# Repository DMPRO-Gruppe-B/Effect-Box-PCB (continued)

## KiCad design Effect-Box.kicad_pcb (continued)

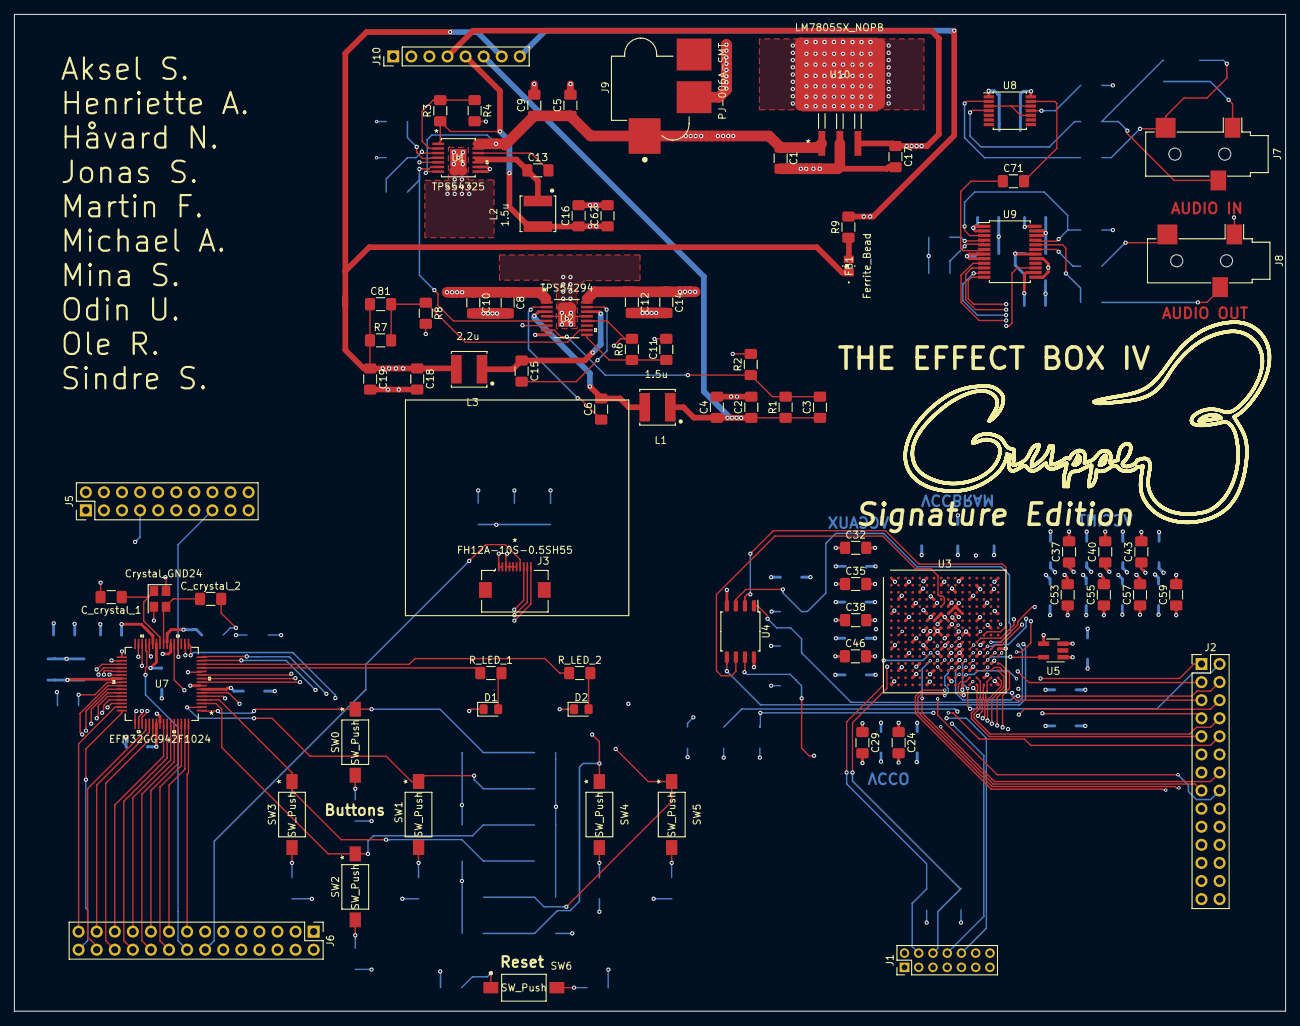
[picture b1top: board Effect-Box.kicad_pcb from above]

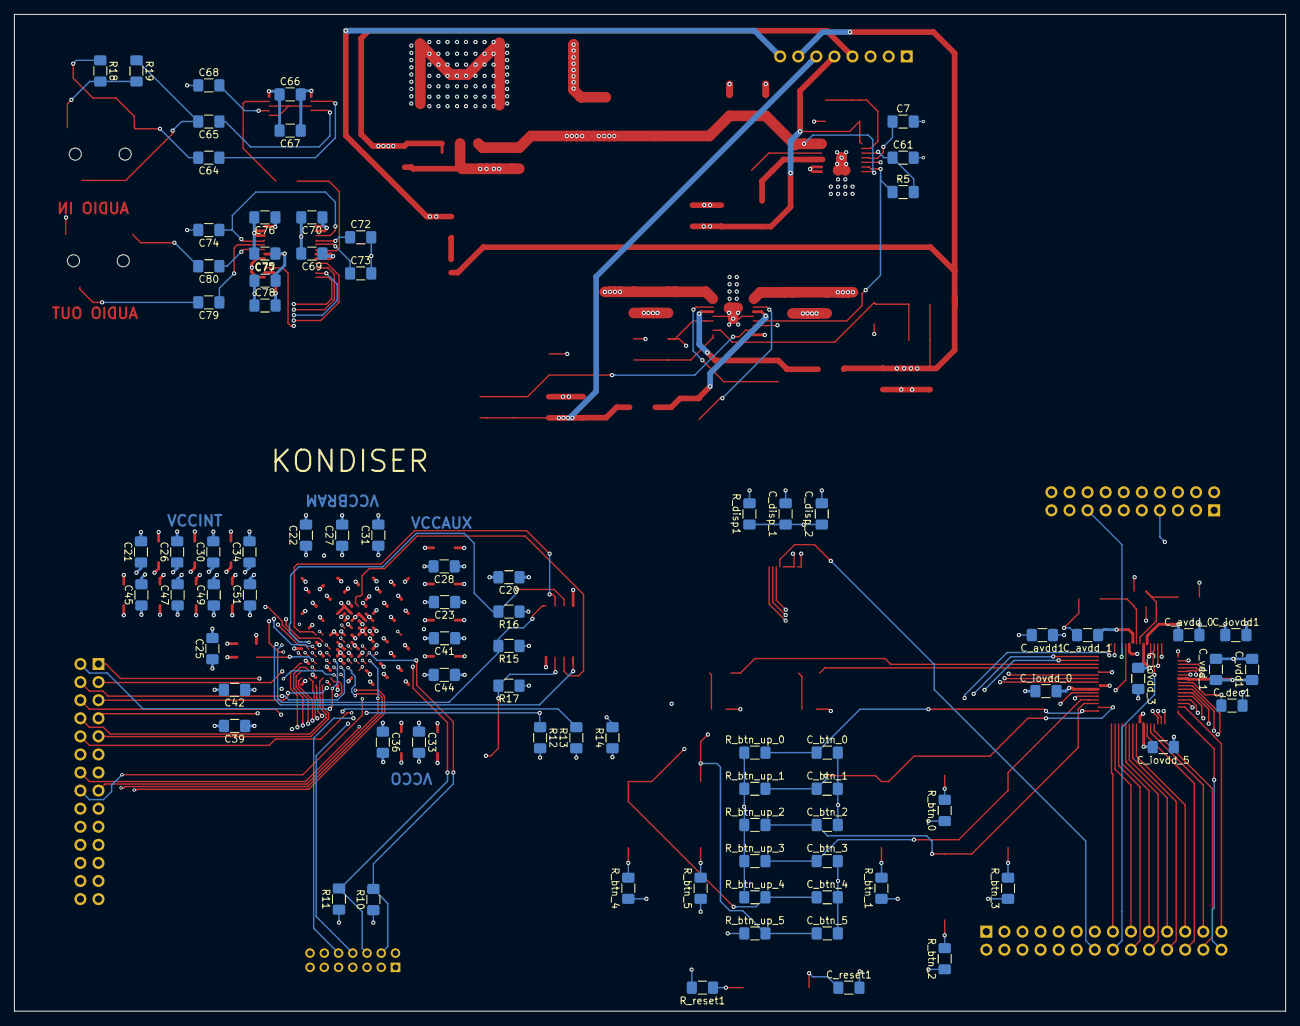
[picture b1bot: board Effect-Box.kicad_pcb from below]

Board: 6 copper layers, 178.6 x 140.0 mm, 161 parts (83 on the bottom side), 134 nets.

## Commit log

2019-09-15 Add .gitignore
2019-09-15 Add separate schema files for subcomponents
2019-09-16 Add FPGA schematic and set up decoupling capacitors
2019-09-16 Backlink to CADLAB.io has been added.
2019-09-17 Add PSU
2019-09-17 Fix PSU warnings
2019-09-17 Update PSU files
2019-09-17 Yeet the bak bois
2019-09-17 Add autoupdated files
    Guess we need this....
2019-09-17 Add capacitors
2019-09-17 Add microcontroller
2019-09-17 Fix all the things
2019-09-17 Add microcontroller cache
2019-09-17 Add avdd capacitors
2019-09-20 Set up FPGA power and enable I/O banks
2019-09-20 Add oscillator
2019-09-20 Remove PSU lib which is apparently merged into (sym_lib_table
2019-09-20 Add PSU lib footprints
2019-09-20 Add footprints for real (such pain)
2019-09-20 Update gitignore
2019-09-20 Use another oscillator, with a custom symbol
2019-09-24 Add lcd schematic
2019-09-24 Move FPGA JTAG schematic to subsheet
2019-09-24 Connect LCD to MCU
2019-09-24 Add JTAG connector
2019-09-24 Switch FPGA I/O banks, and add subsheet for SRAM
2019-09-24 Add FPGA Flash
2019-09-24 Export PSU components as libs
2019-09-24 Change PSU
2019-09-24 Connect SRAM and FPGA
2019-09-24 Fix merge error
2019-09-24 Connect EXTCOMIN to LETIMER
2019-09-24 Change power symbol
2019-09-24 Connect LEDs
2019-09-24 Connect reset button
2019-09-24 Connect button grid
2019-09-24 Add hierarchical labels
2019-09-24 Reorganize FPGA schematic
2019-09-24 Prepare FPGA I/O pins
2019-09-24 Added symbol and library for PCM3003E
2019-09-25 Reorganize libs and add more footprints
2019-09-25 Add more footprints
2019-09-25 Replace footprint
2019-09-25 Update footprints for vregs
2019-09-26 Connect MCU to FPGA
2019-09-26 Add pullup resistors and capacitors to buttons
2019-09-26 Add crystal values
2019-09-26 Add NC symbols
2019-09-26 Add 2x13 pin header
2019-09-26 Fix merge problems
2019-09-26 Added symbols for driver and receiver
2019-09-26 Progress on audio scheme
2019-09-27 More schemes
2019-09-27 Commit including other schemes
2019-09-27 Add PSU 5VA and pin headers and change power symbols
2019-09-27 Add some footprints
2019-09-27 Add input capacitor to 5VA
2019-09-27 Remove extra input capacitors
2019-09-27 Re-add required cap for 5VA
2019-09-27 FPGA cleanup
2019-09-27 Add ferrite bead footprints
2019-09-27 Minor FPGA and MCU fixes
2019-09-27 Add LM7805 symbol and footprint
2019-09-27 All the files
2019-09-27 All the updates
2019-09-27 Add various footprints
2019-09-27 Connect DAC/ADC to FPGA
2019-09-27 Fix LCD connector
2019-09-27 Add audio jack footprint
2019-09-27 Remove USB jack, add power jack
2019-09-27 Wire 5V vreg
2019-09-27 Add button schematic and footprint
2019-09-27 Add led footprint
2019-09-28 Update annotations and footprints
2019-09-28 Organize symbol and footprint files
2019-09-28 Minor unrelated fixes
2019-09-28 Add efm and button footprints
2019-09-28 Minor fixes
2019-09-28 Fix pin headers
2019-09-28 Add lcd footprint
2019-09-28 Fix all footprints
2019-09-28 Add JTAG footprint
2019-09-28 Fix ERC issues
2019-09-28 Add PCBNEW drawing
2019-09-28 Organize components and fix minor issues
2019-09-28 Organize DAC/ADC
2019-09-28 Organize PSU
2019-09-28 Begin moving components to the back plane
2019-09-29 Route DAC/ADC
2019-09-29 Partially route FPGA
2019-09-29 Route PSU
2019-09-29 Partially route MCU
2019-09-29 Route MCU header
2019-09-29 Route rest of MCU header
2019-09-29 Route MCU to FPGA
2019-09-29 Route FPGA to DAC/ADC
2019-09-29 Partially route FPGA pinout
2019-09-29 Set up ground layer
2019-09-29 Set up power layer
2019-09-29 Forgot to save. Fixed some power and routing stuff
2019-09-30 Move vias away from pads around MCU, LCD and buttons
2019-09-30 Recalculate VCC layer
2019-09-30 New via and drill sizes
2019-09-30 Reroute FPGA
2019-09-30 Fix vias for PSU
2019-09-30 Fix vias for audio
2019-09-30 Finish PCB wiring
2019-09-30 Add gruppe b logo
2019-09-30 Add names
2019-09-30 Add edge cuts
2019-09-30 Update GND and VCC fills
2019-10-01 Start fixing PCB
2019-10-02 Add new filled zones
2019-10-02 Fix PSU stuff
2019-10-02 More
2019-10-03 Fix FPGA caps
2019-10-03 Fix FPGA traces
2019-10-03 Fix audio part errors
2019-10-03 Fix MCU
2019-10-03 Fix disconnected invisible pointless object
2019-10-03 Add more power output vias
2019-10-03 Refill zones
2019-10-03 Add more vreg pad thermal vias
2019-10-03 Move silkscreen text away from solder pads
2019-10-03 Fix more silkscreen and reimport from schematic
2019-10-04 Move enev more silkscreen
2019-10-04 Move some silk again
2019-10-08 Add BOM status sheet for keeping track of what is added
2019-10-09 Update BOM status doc
2019-10-09 Update BOM status sheet
